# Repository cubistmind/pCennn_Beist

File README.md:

# ___being_pCB-eist
welcome to the world of my own custom pcB's

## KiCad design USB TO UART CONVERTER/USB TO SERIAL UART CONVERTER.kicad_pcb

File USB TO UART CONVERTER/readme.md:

# USB-to-Serial UART Converter

A custom USB-to-UART converter PCB designed using **KiCad 10.0.04**.

This project implements a USB-to-serial communication interface using the FT232RL USB-to-UART bridge IC. The PCB provides a USB Mini-B connection and a dedicated UART output header for interfacing with external embedded systems, microcontrollers, and development boards.

## Project Overview

| Parameter | Specification |
|---|---|
| Project | USB-to-Serial UART Converter |
| Main IC | FT232RL |
| USB Connector | Mini-B |
| Communication | USB to UART |
| PCB Layers | 2-layer |
| EDA Software | KiCad 10 |
| Design Type | Custom PCB |
| PCB Fabrication | Gerber and Excellon outputs included |

## Features

- FT232RL-based USB-to-UART conversion
- USB Mini-B interface
- Dedicated 6-pin UART output connector
- RGB LED indicator
- Through-hole and SMD components
- Four PCB mounting holes
- Two-layer PCB design
- Front and back copper routing
- Manufacturing-ready Gerber and drill outputs

## Hardware Components

| Component | Description |
|---|---|
| U1 | FT232RL USB-to-UART bridge |
| J1 | USB Mini-B connector |
| J2 | 3-pin jumper |
| J3 | 6-pin UART output |
| D1 | RGB LED |
| FB1 | Ferrite bead |
| R1–R3 | Resistors |
| C1–C5 | Capacitors |

Refer to `BOM.csv` for the component list and footprints.

## PCB Design

The PCB was designed and routed in KiCad 10.

The design includes:
- Front copper layer (F.Cu)
- Back copper layer (B.Cu)
- Front and back solder masks
- Front and back silkscreen
- Defined board outline
- Plated and non-plated drill holes

## Design Verification

The design was checked using KiCad's Electrical Rules Checker (ERC) and Design Rules Checker (DRC).

**Reported verification status:**
- ERC: 0 errors, 0 warnings
- DRC: 0 errors, 0 warnings

These results indicate that the configured schematic and PCB design checks passed. Physical hardware operation still requires fabrication and functional testing.

## Repository Structure

```text
USB-to-Serial-UART-Converter/
│
├── USB TO SERIAL UART CONVERTER.kicad_pro
├── USB TO SERIAL UART CONVERTER.kicad_sch
├── USB TO SERIAL UART CONVERTER.kicad_pcb
│
├── BOM.csv
│
├── GERBER/
│   ├── F_Cu.gtl
│   ├── B_Cu.gbl
│   ├── F_Mask.gts
│   ├── B_Mask.gbs
│   ├── F_Silkscreen.gto
│   ├── B_Silkscreen.gbo
│   ├── Edge_Cuts.gm1
│   ├── PTH.drl
│   ├── NPTH.drl
│   └── Gerber job file
│
└── README.md
```

## Manufacturing

The repository includes Gerber fabrication files and Excellon drill files for a two-layer PCB.

For PCB fabrication, provide the manufacturer with the complete Gerber and drill file set.

For PCBA, additionally prepare:
- Verified BOM with manufacturer part numbers
- Component Placement List (CPL)
- Solder-paste stencil files, where required

## Getting Started

1. Clone or download this repository.
2. Open the `.kicad_pro` file using KiCad 10.
3. Inspect the schematic and PCB layout.
4. Review the BOM and manufacturing outputs.
5. Generate updated Gerber files if the design is modified.

## Project Status

**PCB Design: Completed**

**ERC/DRC: Passed according to the latest project checks**

**Physical Hardware Testing: Pending**

## License

Add your preferred open-source hardware license before distributing or manufacturing derivative designs.

---

Designed with KiCad 10.

**USB-to-Serial UART Converter | Electronics & PCB Design Project**

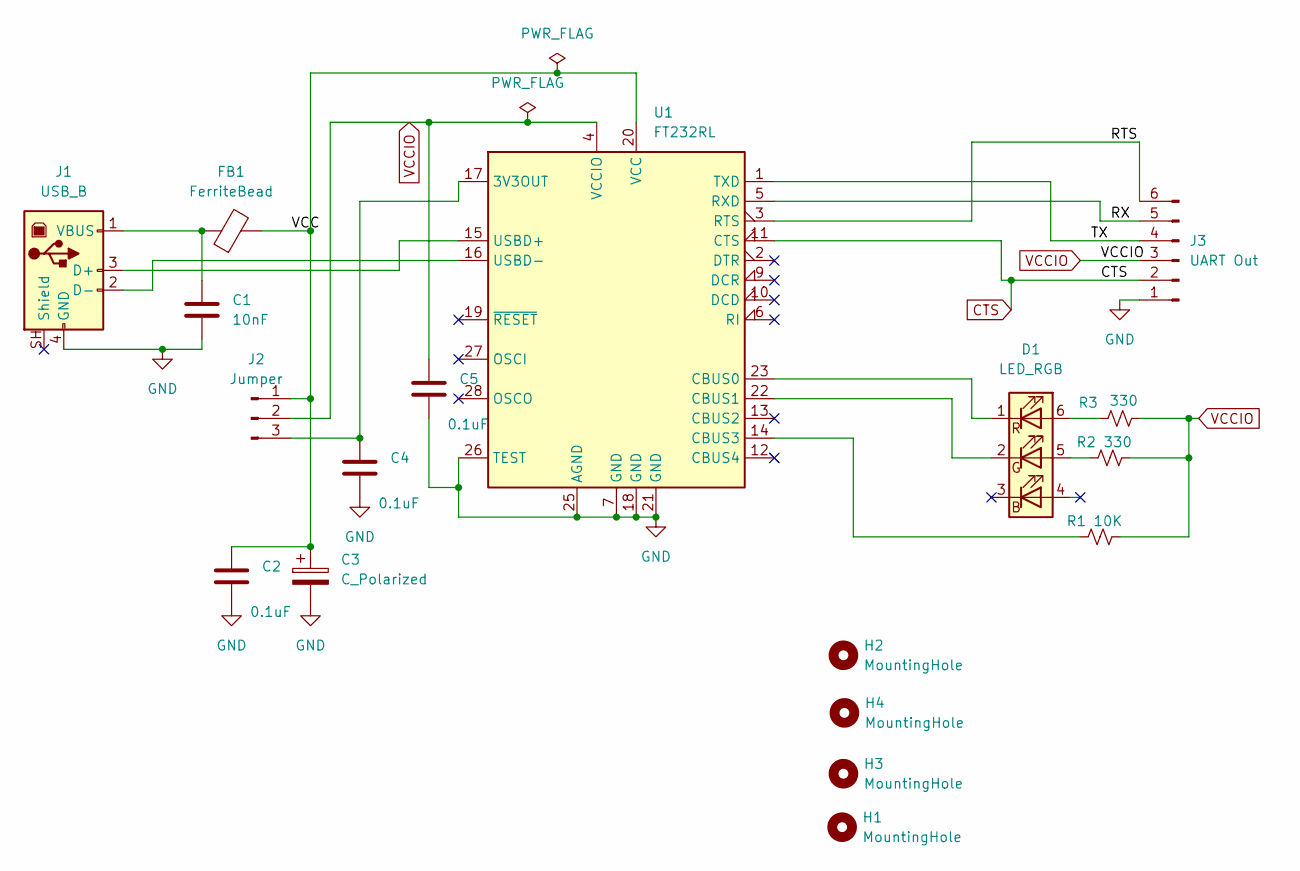
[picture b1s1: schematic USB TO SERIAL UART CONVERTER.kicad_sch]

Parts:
C1: 10nF; CP_Radial_D4.0mm_P1.50mm
C2, C4, C5: 0.1uF; CP_Radial_D4.0mm_P1.50mm
C3: C_Polarized; CP_Radial_D4.0mm_P1.50mm
D1: LED_RGB; LED_RGB_5050-6
FB1: FerriteBead; LairdTech_28C0236-0JW-10
H1, H2, H3, H4: MountingHole; MountingHole_3.2mm_M3_DIN965_Pad
J1: USB_B; USB_Mini-B_Lumberg_2486_01_Horizontal
J2: Jumper; PinHeader_1x03_P1.00mm_Vertical
J3: UART Out; PinHeader_1x06_P1.00mm_Vertical_SMD_Pin1Left
R1: 10K; R_Axial_DIN0204_L3.6mm_D1.6mm_P7.62mm_Horizontal
R2, R3: 330; R_Axial_DIN0204_L3.6mm_D1.6mm_P7.62mm_Horizontal
U1: FT232RL; SSOP-28_5.3x10.2mm_P0.65mm

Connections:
/RTS: J3.6, U1.3 (RTS)
/RX: J3.5, U1.5 (RXD)
/TX: J3.4, U1.1 (TXD)
/VCC: C2.1, C3.1, FB1.2, J2.1, U1.20 (VCC)
CTS: J3.2, U1.11 (CTS)
GND: C1.2, C2.2, C3.2, C4.2, C5.2, J1.4 (GND), J3.1, U1.7 (GND), U1.18 (GND), U1.21 (GND), U1.25 (AGND), U1.26 (TEST)
unnamed: D1.5 (GA), R2.1
unnamed: D1.2 (GK), U1.22 (CBUS1)
unnamed: D1.6 (RA), R3.1
unnamed: D1.1 (RK), U1.23 (CBUS0)
unnamed: J1.3 (D+), U1.15 (USBD+)
unnamed: J1.2 (D-), U1.16 (USBD-)
unnamed: C1.1, FB1.1, J1.1 (VBUS)
unnamed: C4.1, J2.3, U1.17 (3V3OUT)
unnamed: R1.1, U1.14 (CBUS3)
VCCIO: C5.1, J2.2, J3.3, R1.2, R2.2, R3.2, U1.4 (VCCIO)

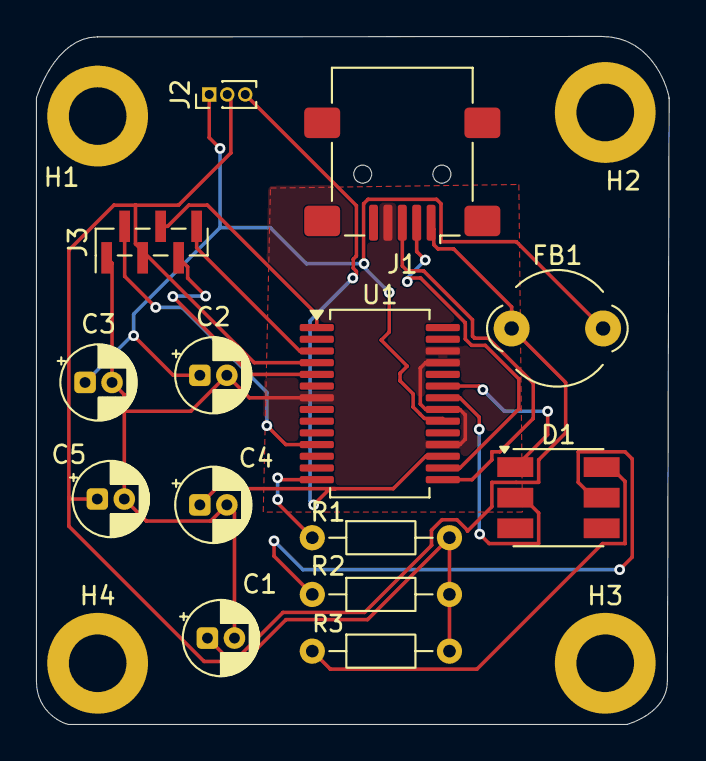
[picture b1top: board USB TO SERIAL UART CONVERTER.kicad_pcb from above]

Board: 2 copper layers, 35.1 x 38.2 mm, 18 parts (0 on the bottom side), 16 nets.

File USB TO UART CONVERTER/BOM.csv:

Reference,Quantity,Value,Footprint,Manufacturer Part Number
U1,1,FT232RL,Package_SO:SSOP-28_5.3x10.2mm_P0.65mm,
J1,1,USB_B,Connector_USB:USB_Mini-B_Lumberg_2486_01_Horizontal,
J2,1,Jumper,Connector_PinHeader_1.00mm:PinHeader_1x03_P1.00mm_Vertical,
J3,1,UART Out,Connector_PinHeader_1.00mm:PinHeader_1x06_P1.00mm_Vertical_SMD_Pin1Left,
FB1,1,FerriteBead,Ferrite_THT:LairdTech_28C0236-0JW-10,
D1,1,LED_RGB,LED_SMD:LED_RGB_5050-6,
C1,1,10nF,Capacitor_THT:CP_Radial_D4.0mm_P1.50mm,
C2 C4 C5,3,0.1uF,Capacitor_THT:CP_Radial_D4.0mm_P1.50mm,
C3,1,C_Polarized,Capacitor_THT:CP_Radial_D4.0mm_P1.50mm,
R1,1,10K,Resistor_THT:R_Axial_DIN0204_L3.6mm_D1.6mm_P7.62mm_Horizontal,
R2 R3,2,330,Resistor_THT:R_Axial_DIN0204_L3.6mm_D1.6mm_P7.62mm_Horizontal,
